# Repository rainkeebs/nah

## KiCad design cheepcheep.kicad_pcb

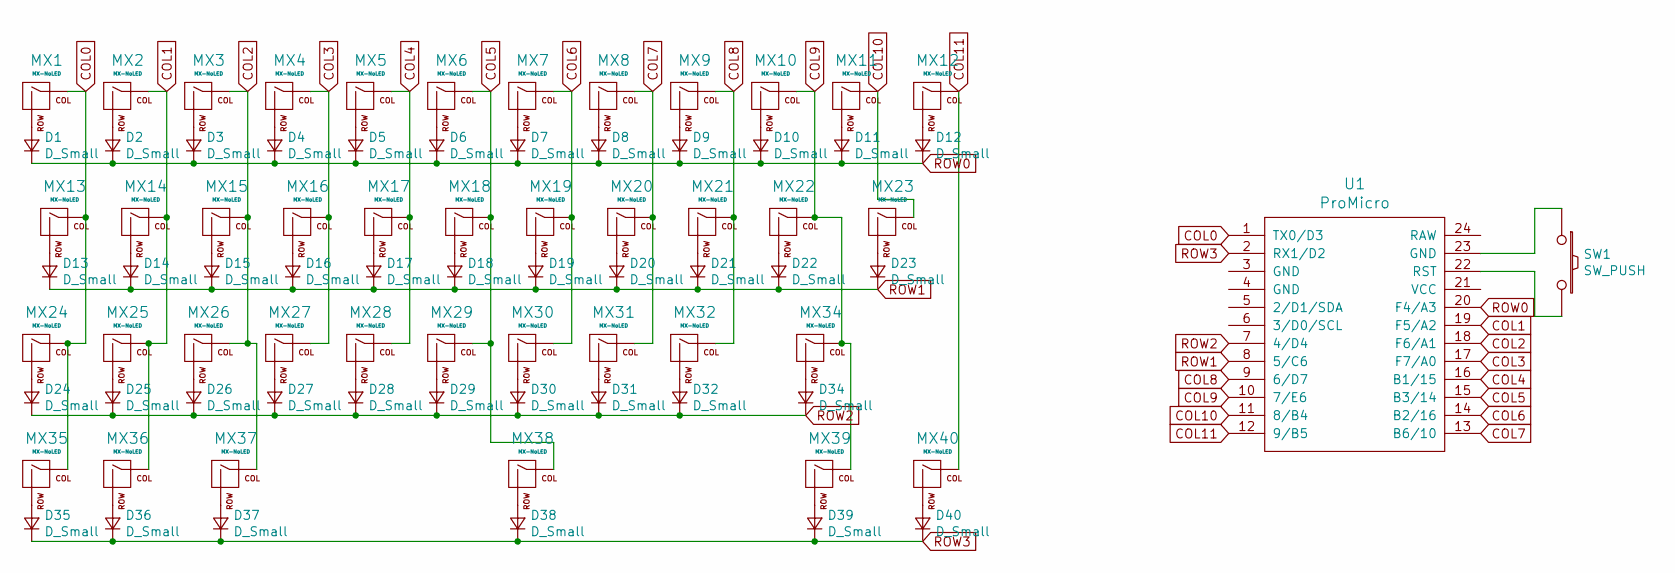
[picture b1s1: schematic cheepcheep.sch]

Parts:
D1, D2, D3, D4, D5, D6, D7, D8, D9, D10, D11, D12, D13, D14, D15, D16, D17, D18, D19, D20, D21, D22, D23, D24, D25, D26, D27, D28, D29, D30, D31, D32, D34, D35, D36, D37, D38, D39, D40: D_Small; D_DO-35_SOD27_P7.62mm_Horizontal
MX1, MX2, MX3, MX4, MX5, MX6, MX7, MX8, MX9, MX10, MX11, MX12, MX14, MX15, MX16, MX17, MX18, MX19, MX20, MX21, MX22, MX25, MX26, MX27, MX28, MX29, MX30, MX31, MX32, MX37, MX39: MX-NoLED; MXOnly-1U-NoLED
MX13, MX23: MX-NoLED; MXOnly-1.5U-NoLED
MX24, MX34: MX-NoLED; MXOnly-2U-NoLED
MX35, MX36, MX40: MX-NoLED; MXOnly-1.25U-NoLED
MX38: MX-NoLED; MXOnly-6.25U-ReversedStabilizers-NoLED
SW1: SW_PUSH; SKQG-1155865
U1: ProMicro; ArduinoProMicro

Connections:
COL0: MX1.1 (COL), MX13.1 (COL), MX24.1 (COL), MX35.1 (COL), U1.1 (TX0/D3)
COL1: MX2.1 (COL), MX14.1 (COL), MX25.1 (COL), MX36.1 (COL), U1.19 (F5/A2)
COL2: MX3.1 (COL), MX15.1 (COL), MX26.1 (COL), MX37.1 (COL), U1.18 (F6/A1)
COL3: MX4.1 (COL), MX16.1 (COL), MX27.1 (COL), U1.17 (F7/A0)
COL4: MX5.1 (COL), MX17.1 (COL), MX28.1 (COL), U1.16 (B1/15)
COL5: MX6.1 (COL), MX18.1 (COL), MX29.1 (COL), MX38.1 (COL), U1.15 (B3/14)
COL6: MX7.1 (COL), MX19.1 (COL), MX30.1 (COL), U1.14 (B2/16)
COL7: MX8.1 (COL), MX20.1 (COL), MX31.1 (COL), U1.13 (B6/10)
COL8: MX9.1 (COL), MX21.1 (COL), MX32.1 (COL), U1.9 (6/D7)
COL9: MX10.1 (COL), MX22.1 (COL), MX34.1 (COL), MX39.1 (COL), U1.10 (7/E6)
COL10: MX11.1 (COL), MX23.1 (COL), U1.11 (8/B4)
COL11: MX12.1 (COL), MX40.1 (COL), U1.12 (9/B5)
unnamed: D1.2 (A), MX1.2 (ROW)
unnamed: D2.2 (A), MX2.2 (ROW)
unnamed: D3.2 (A), MX3.2 (ROW)
unnamed: D4.2 (A), MX4.2 (ROW)
unnamed: D5.2 (A), MX5.2 (ROW)
unnamed: D6.2 (A), MX6.2 (ROW)
unnamed: D7.2 (A), MX7.2 (ROW)
unnamed: D8.2 (A), MX8.2 (ROW)
unnamed: D9.2 (A), MX9.2 (ROW)
unnamed: D10.2 (A), MX10.2 (ROW)
unnamed: D11.2 (A), MX11.2 (ROW)
unnamed: D12.2 (A), MX12.2 (ROW)
unnamed: D13.2 (A), MX13.2 (ROW)
unnamed: D14.2 (A), MX14.2 (ROW)
unnamed: D15.2 (A), MX15.2 (ROW)
unnamed: D16.2 (A), MX16.2 (ROW)
unnamed: D17.2 (A), MX17.2 (ROW)
unnamed: D18.2 (A), MX18.2 (ROW)
unnamed: D19.2 (A), MX19.2 (ROW)
unnamed: D20.2 (A), MX20.2 (ROW)
unnamed: D21.2 (A), MX21.2 (ROW)
unnamed: D22.2 (A), MX22.2 (ROW)
unnamed: D23.2 (A), MX23.2 (ROW)
unnamed: D24.2 (A), MX24.2 (ROW)
unnamed: D25.2 (A), MX25.2 (ROW)
unnamed: D26.2 (A), MX26.2 (ROW)
unnamed: D27.2 (A), MX27.2 (ROW)
unnamed: D28.2 (A), MX28.2 (ROW)
unnamed: D29.2 (A), MX29.2 (ROW)
unnamed: D30.2 (A), MX30.2 (ROW)
unnamed: D31.2 (A), MX31.2 (ROW)
unnamed: D32.2 (A), MX32.2 (ROW)
unnamed: D34.2 (A), MX34.2 (ROW)
unnamed: D35.2 (A), MX35.2 (ROW)
unnamed: D36.2 (A), MX36.2 (ROW)
unnamed: D37.2 (A), MX37.2 (ROW)
unnamed: D38.2 (A), MX38.2 (ROW)
unnamed: D39.2 (A), MX39.2 (ROW)
unnamed: D40.2 (A), MX40.2 (ROW)
unnamed: SW1.1, U1.23 (GND)
unnamed: SW1.2, U1.22 (RST)
ROW0: D1.1 (K), D2.1 (K), D3.1 (K), D4.1 (K), D5.1 (K), D6.1 (K), D7.1 (K), D8.1 (K), D9.1 (K), D10.1 (K), D11.1 (K), D12.1 (K), U1.20 (F4/A3)
ROW1: D13.1 (K), D14.1 (K), D15.1 (K), D16.1 (K), D17.1 (K), D18.1 (K), D19.1 (K), D20.1 (K), D21.1 (K), D22.1 (K), D23.1 (K), U1.8 (5/C6)
ROW2: D24.1 (K), D25.1 (K), D26.1 (K), D27.1 (K), D28.1 (K), D29.1 (K), D30.1 (K), D31.1 (K), D32.1 (K), D34.1 (K), U1.7 (4/D4)
ROW3: D35.1 (K), D36.1 (K), D37.1 (K), D38.1 (K), D39.1 (K), D40.1 (K), U1.2 (RX1/D2)

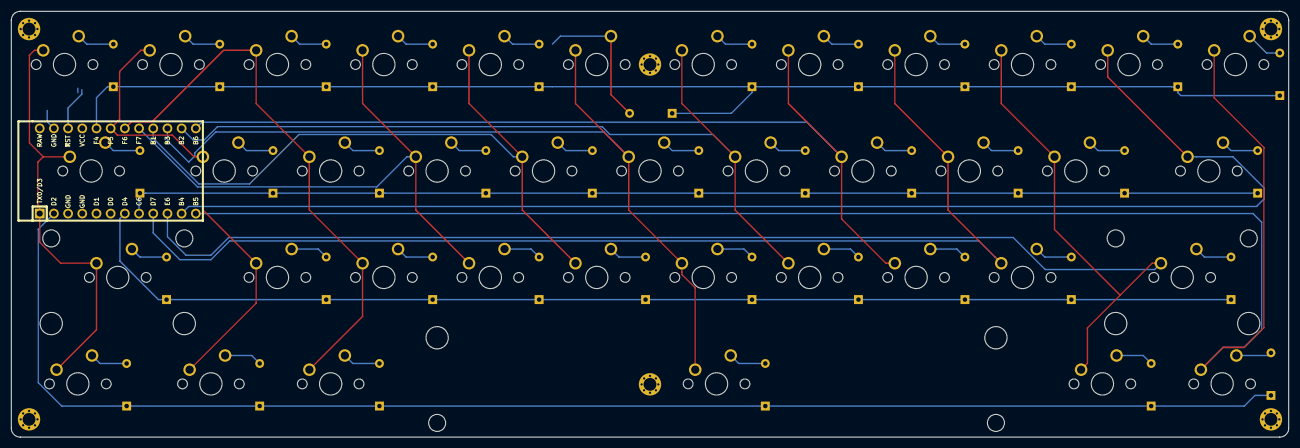
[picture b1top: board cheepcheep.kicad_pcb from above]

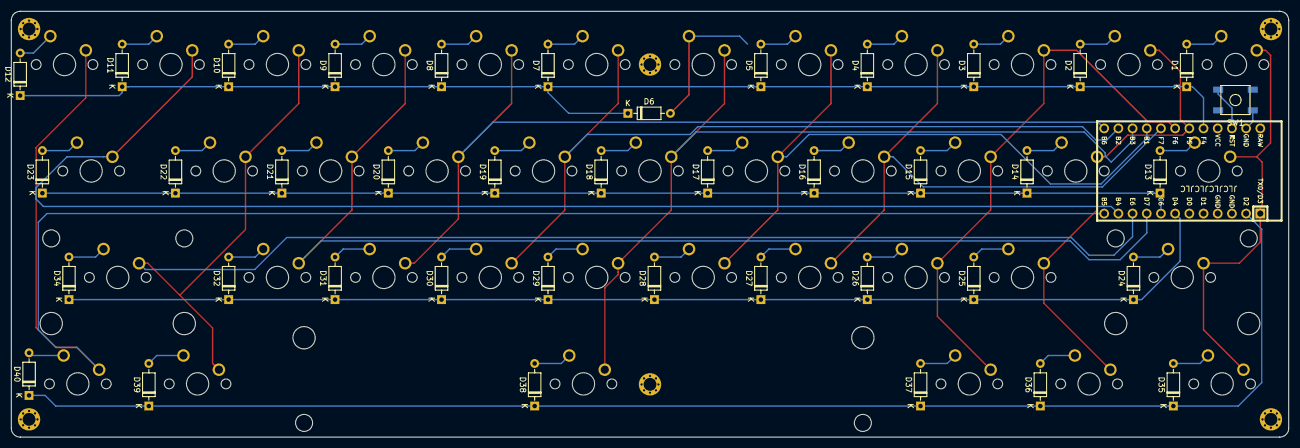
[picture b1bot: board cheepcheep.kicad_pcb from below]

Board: 2 copper layers, 228.6 x 76.2 mm, 86 parts (40 on the bottom side), 57 nets.

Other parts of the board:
Ref**: Val**; M2_HOLE_v3
Ref**#2, Ref**#3, Ref**#4, Ref**#5, Ref**#6: Val**; M2_HOLE_v3

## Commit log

2020-10-25 initial ig
2020-10-26 dropped
